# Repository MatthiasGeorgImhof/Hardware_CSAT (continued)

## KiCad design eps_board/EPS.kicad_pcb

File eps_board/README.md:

# Electric Power Supply (EPS) board

- STM32L496VGTx controller
- 2x CAN buses
- 2x 18650 LiPo batteries for operation and 1x CR2450 cell for RTC

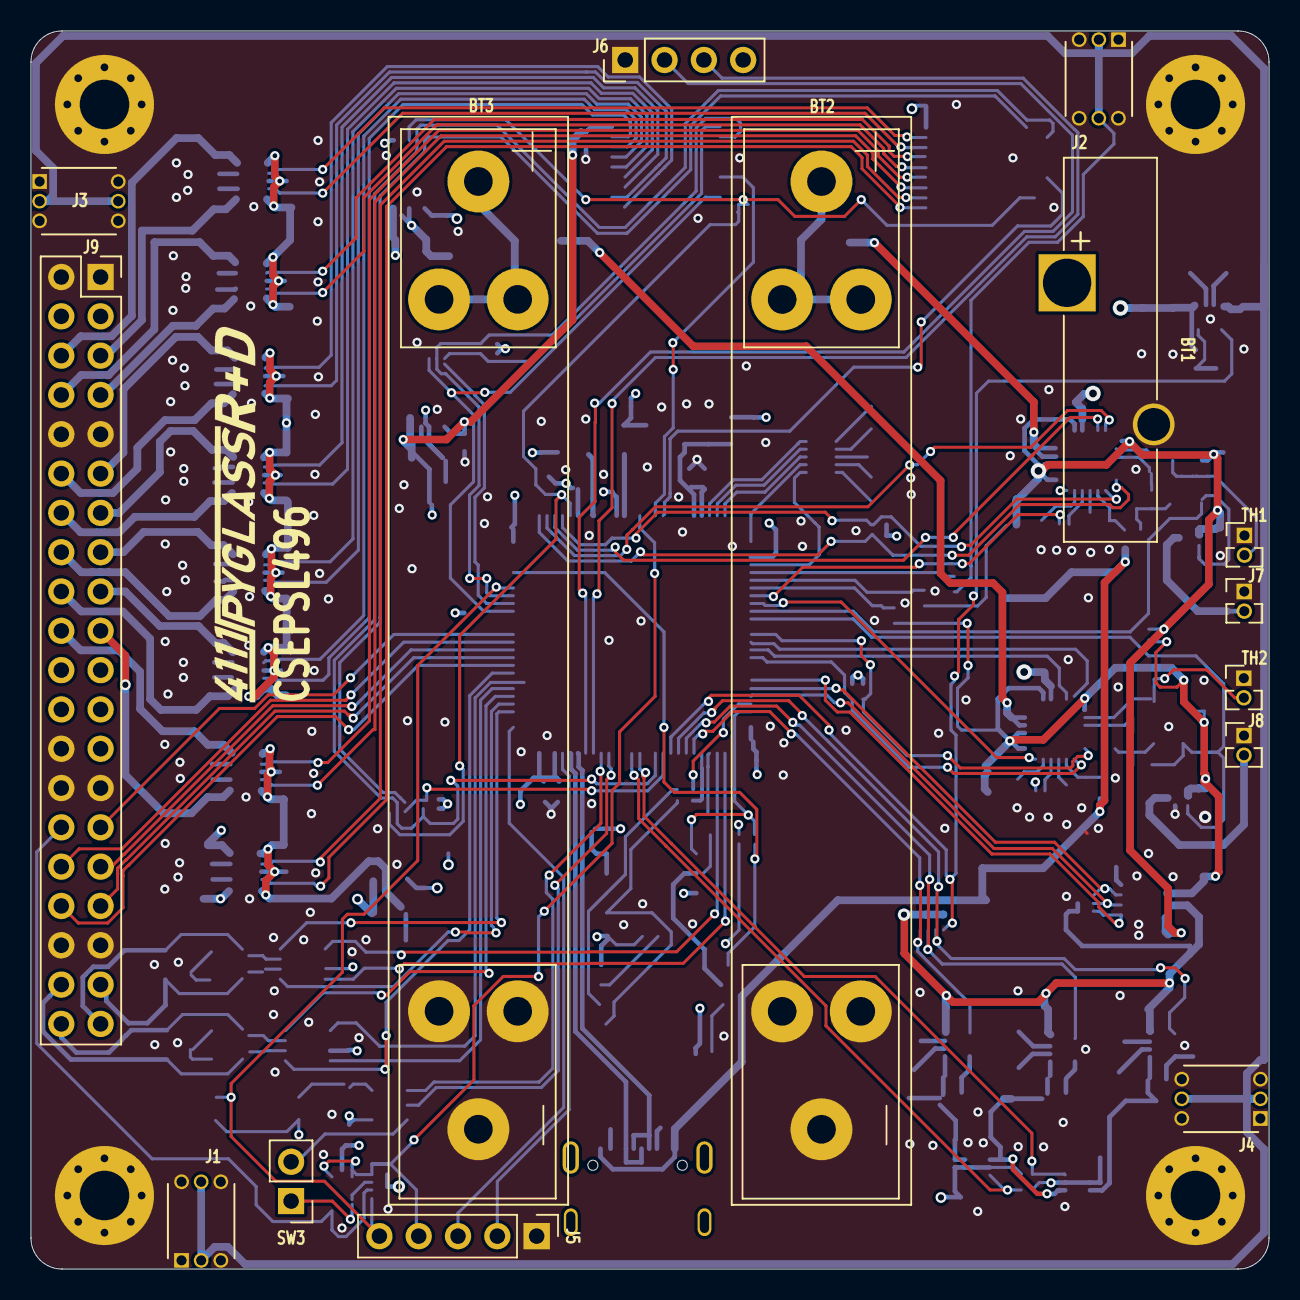
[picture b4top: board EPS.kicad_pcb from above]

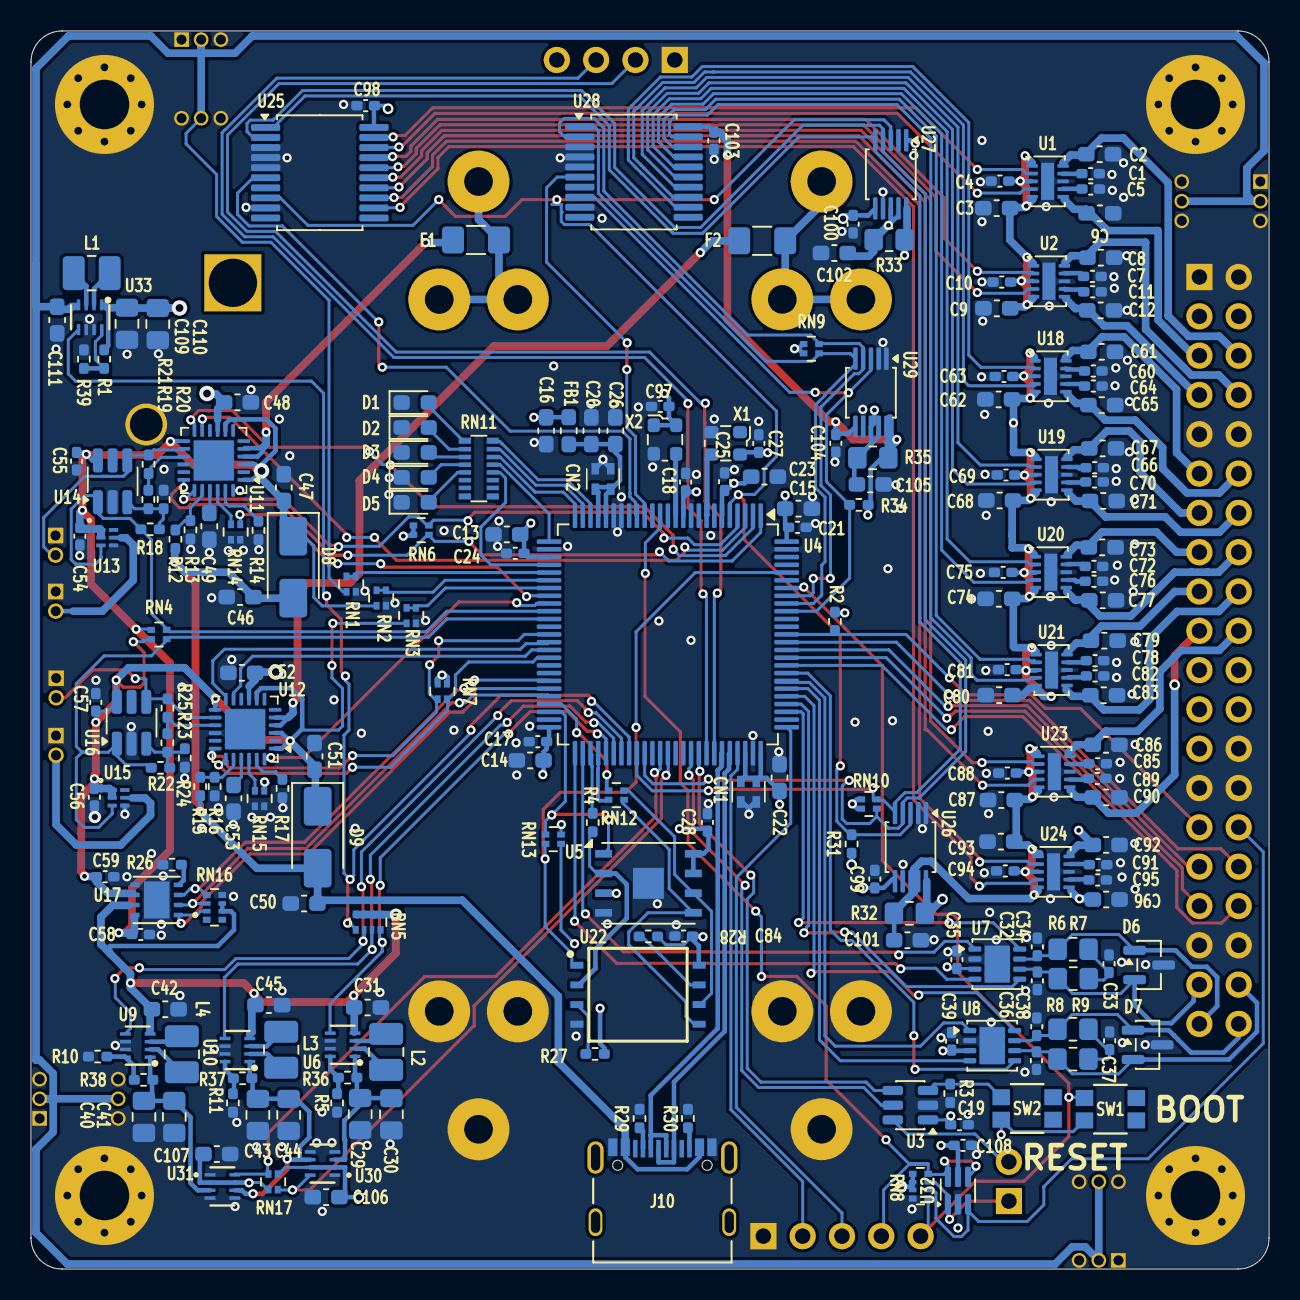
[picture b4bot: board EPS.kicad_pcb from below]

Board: 4 copper layers, 80.0 x 80.0 mm, 242 parts (223 on the bottom side), 187 nets.

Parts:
BT1: CR2450; Battery_Panasonic_CR2450-VAN_Vertical_CircularHoles
BT2, BT3: Battery_Cell; BatteryHolder_Keystone_54_v2_1x18650
C1, C5, C7, C11, C60, C64, C66, C70, C72, C76, C78, C82, C85, C89, C91, C95: 220pF; C_0402_1005Metric_Pad0.74x0.62mm_HandSolder
C2, C6, C8, C12, C61, C65, C67, C71, C73, C77, C79, C83, C86, C90, C92, C96: 10u; C_0603_1608Metric_Pad1.08x0.95mm_HandSolder
C3, C9, C62, C68, C74, C80, C87, C93: 22u; C_0603_1608Metric_Pad1.08x0.95mm_HandSolder
C4, C10, C27, C28, C35, C39, C63, C69, C75, C81, C84, C88, C94, C97, C108: 100n; C_0402_1005Metric_Pad0.74x0.62mm_HandSolder
C13, C14, C15, C16, C20, C22, C23, C26, C101, C102, C105, C106, C107: 10uF; C_0603_1608Metric_Pad1.08x0.95mm_HandSolder
C17, C18, C19, C21, C24, C25, C54, C55, C56, C57, C58, C59, C98, C99, C100, C103, C104: 100nF; C_0402_1005Metric_Pad0.74x0.62mm_HandSolder
C29, C30, C40, C41, C43, C44, C109, C110: 47uF; C_0805_2012Metric_Pad1.18x1.45mm_HandSolder
C31, C42, C45, C111: 22uF; C_0603_1608Metric_Pad1.08x0.95mm_HandSolder
C32, C34, C36, C38: 100p; C_0402_1005Metric_Pad0.74x0.62mm_HandSolder
C33, C37: 4n7; C_0402_1005Metric_Pad0.74x0.62mm_HandSolder
C46, C47, C48, C49, C50, C51, C52, C53: 4.7uF; C_0603_1608Metric_Pad1.08x0.95mm_HandSolder
CN1, CN2: 100nF; W2A2-X
D1: RED; LED_0603_1608Metric_Pad1.05x0.95mm_HandSolder
D2: GREEN; LED_0603_1608Metric_Pad1.05x0.95mm_HandSolder
D3, D4, D5: YELLOW; LED_0603_1608Metric_Pad1.05x0.95mm_HandSolder
D6, D7: NUP2105LT1G; SOT-23
D8, D9: NRVBA210LNT3G; D_SMA
F1, F2: Polyfuse; Fuse_1206_3216Metric_Pad1.42x1.75mm_HandSolder
FB1: 120R; L_0603_1608Metric_Pad1.05x0.95mm_HandSolder
H1, H2, H3, H4: MountingHole_Pad; MountingHole_3.2mm_M3_Pad_Via
J1, J2, J3, J4: Conn_02x03_Odd_Even; HARWIN_M50-3200345
J5: Conn_01x05_Pin Vertical; PinHeader_1x05_P2.54mm_Vertical
J6: Conn_01x04_Pin Vertical; PinHeader_1x04_P2.54mm_Vertical
J7, J8: Conn_01x02; PinHeader_1x02_P1.27mm_Vertical
J9: PC104 Conn_02x20_Odd_Even; PinSocket_2x20_P2.54mm_Vertical
J10: 10155435-00011LF; AMPHENOL_10155435-00011LF
L1, L2, L3, L4: 1uH; L_1008_2520Metric_Pad1.43x2.20mm_HandSolder
R1: 806K; R_0402_1005Metric_Pad0.72x0.64mm_HandSolder
R2: 330K; R_0402_1005Metric_Pad0.72x0.64mm_HandSolder
R3: 22K; R_0402_1005Metric_Pad0.72x0.64mm_HandSolder
R4: 22R; R_0402_1005Metric_Pad0.72x0.64mm_HandSolder
R5, R10, R11, R39: 91K; R_0402_1005Metric_Pad0.72x0.64mm_HandSolder
R6, R7, R8, R9: 60R4; R_0805_2012Metric_Pad1.20x1.40mm_HandSolder
R12, R15: 26.7K; R_0402_1005Metric_Pad0.72x0.64mm_HandSolder
R13, R16, R21, R25: 10K; R_0402_1005Metric_Pad0.72x0.64mm_HandSolder
R14, R17: 1M; R_0402_1005Metric_Pad0.72x0.64mm_HandSolder
R18, R22: DNP; R_0402_1005Metric_Pad0.72x0.64mm_HandSolder
R19, R23, R27, R28, R31, R34: 100K; R_0402_1005Metric_Pad0.72x0.64mm_HandSolder
R20, R24: 280K; R_0402_1005Metric_Pad0.72x0.64mm_HandSolder
R26: 330R; R_0402_1005Metric_Pad0.72x0.64mm_HandSolder
R29, R30: 5K1; R_0402_1005Metric_Pad0.72x0.64mm_HandSolder
R32, R33, R35: 10m; R_0805_2012Metric_Pad1.20x1.40mm_HandSolder
R36, R38: 511K; R_0402_1005Metric_Pad0.72x0.64mm_HandSolder
R37: 490K; R_0402_1005Metric_Pad0.72x0.64mm_HandSolder
RN1, RN2, RN3, RN4, RN6, RN7, RN13: 100K; R_Array_Convex_2x0402_widepads
RN5, RN8, RN16: 100K; R_Array_Convex_4x0402_widepads
RN9, RN10: 5K6; R_Array_Convex_2x0402_widepads
RN11: 1K; R_Array_Convex_8x0602_widepads
RN12: 22R; R_Array_Convex_2x0402_widepads
RN14, RN15, RN17: 10K; R_Array_Convex_2x0402_widepads
SW1, SW2: EVP-AA602W; EVP602AA
SW3: Conn_01x02_Pin Vertical; PinHeader_1x02_P2.54mm_Vertical
TH1, TH2: Thermistor_NTC; PinHeader_1x02_P1.27mm_Vertical
U1, U2, U18, U19, U20, U21, U23, U24: TPS22968QDMGRQ1; WSON-10-1EP_2x3mm_P0.5mm_EP0.84x2.4mm
U3: TPL5010; SOT-23-6
U4: STM32L496VGTx; LQFP-100_14x14mm_P0.5mm
U5: MR25H10; DFN-8-1EP_6x5mm_P1.27mm_EP2x2mm
U6, U9, U10, U33: TPS631000DRLR; TPS631000DRLR_TEX
U7, U8: TCAN3414; VSON-8-1EP_3x3mm_P0.65mm_EP1.65x2.4mm
U11, U12: LTC4066; QFN-24-1EP_4x4mm_P0.5mm_EP2.6x2.6mm
U13, U15: TPS22995; WQFN-HR6_RZG_TEX
U14, U16: MCP65R46; SOT-23-6_Handsoldering
U17: TPS2115ADRBR; SON65P300X300X100-9N
U22: MT29F4G01ABAFDWB-IT:F TR; SON127P800X600X65-8N
U25, U28: MCP23008T-E/SS; SSOP-20_5.3x7.2mm_P0.65mm
U26, U27: INA226AIDGSR; VSSOP-10_3x3mm_P0.5mm
U29: INA226; VSSOP-10_3x3mm_P0.5mm
U30, U31: LM66200DRLR; SOT-5X3_DRL_TEX
U32: 74LVC2G07; SOT-363_SC-70-6
X1: 32.768KHZ; Oscillator_SMD_ECS_2520MV-xxx-xx-4Pin_2.5x2.0mm
X2: 10MHz; Oscillator_SMD_ECS_2520MV-xxx-xx-4Pin_2.5x2.0mm

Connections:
+3V3: C103.1, C104.1, C107.1, R34.1, R35.1, RN17.3 (R2.2), U28.20 (VDD), U29.6 (VS), U29.10 (IN+), U31.2 (VOUT), U31.7 (VOUT)
+3V3_CORE: C13.1, C14.1, C15.1, C16.1, C17.1, C18.1, C19.1, C21.2, C22.2, C24.1, C27.1, C35.1, C39.1, C97.1, C98.1, C99.1, C100.1, C106.1, C108.2, CN1.1, CN1.2, FB1.1, J6.4, R2.1, R31.1, R32.1, RN6.1 (R1.1), RN6.2 (R2.1), RN7.1 (R1.1), RN7.2 (R2.1), RN8.5 (R4.2), RN8.6 (R3.2), RN8.7 (R2.2), RN9.1 (R1.1), RN9.2 (R2.1), RN10.1 (R1.1), RN10.2 (R2.1), RN17.1 (R1.1), SW1.2, SW2.2, U3.1 (VDD), U4.11 (VDD), U4.28 (VDD), U4.50 (VDD), U4.73 (VDDUSB), U4.75 (VDD), U4.100 (VDD), U7.3 (VCC), U8.3 (VCC), U25.20 (VDD), U26.6 (VS), U26.10 (IN+), U27.1 (A1), U27.6 (VS), U30.2 (VOUT), U30.7 (VOUT), U32.5 (VCC), X1.4 (VCC), X2.1 (TRI-STATE), X2.4 (VDD)
/3V3_1: C61.1, J9.11, U18.10 (VOUT1)
/3V3_2: C65.2, J9.12, U18.6 (VOUT2)
/3V3_3: C67.1, J9.13, U19.10 (VOUT1)
/3V3_4: C71.2, J9.14, U19.6 (VOUT2)
/3V3_5: C73.1, J9.15, U20.10 (VOUT1)
/3V3_6: C77.2, J9.16, U20.6 (VOUT2)
/3V3_7: C79.1, J9.17, U21.10 (VOUT1)
/3V3_8: C83.2, J9.18, U21.6 (VOUT2)
/3V3_9: C90.2, J9.19, U23.6 (VOUT2)
/3V3_10: C86.1, J9.20, U23.10 (VOUT1)
/3V3_EPS_FLASH: C84.1, C96.2, R27.1, R28.1, RN13.1 (R1.1), U22.8 (VCC), U24.6 (VOUT2)
/3V3_EPS_MRAM: C28.1, C92.1, RN13.2 (R2.1), U5.3 (~WP), U5.7 (~HOLD), U5.8 (VDD), U24.10 (VOUT1)
/*BC_1_CHRG: RN6.3 (R2.2), U4.1 (PE2), U11.18 (~CHRG)
/*BC_2_CHRG: RN7.3 (R2.2), U4.38 (PE7), U12.18 (~CHRG)
/*IDEAL_STATUS: RN16.3 (R3.1), U4.44 (PE13), U17.1 (STAT)
/ADC_SOLAR_RAW: RN1.3 (R2.2), RN1.4 (R1.2), U4.30 (PA5)
/ADC_VOUT1: RN2.3 (R2.2), RN2.4 (R1.2), U4.31 (PA6)
/ADC_VOUT2: RN3.3 (R2.2), RN3.4 (R1.2), U4.32 (PA7)
/ATTENTION: J9.29, R2.2, U4.88 (PD7)
/AVI_EXTRN_RST: J9.32, U4.87 (PD6)
/BATTERY_1/NTC: R21.2, TH1.2, U11.14 (NTC), U14.4 (-)
/BATTERY_1/VBAT: F1.1, U11.4 (BAT), U11.5 (BAT)
/BATTERY_1/VNTC: R19.1, R21.1, U11.15 (VNTC)
/BATTERY_2/NTC: R25.2, TH2.2, U12.14 (NTC), U16.4 (-)
/BATTERY_2/VBAT: F2.1, U12.4 (BAT), U12.5 (BAT)
/BATTERY_2/VNTC: R23.1, R25.1, U12.15 (VNTC)
/BATTERY_CHARGER_1/CLPROG: RN14.2 (R2.1), U11.22 (CLPROG)
/BATTERY_CHARGER_2/CLPROG: RN15.2 (R2.1), U12.22 (CLPROG)
/BATT_1: C6.2, J9.5, U1.6 (VOUT2)
/BATT_2: C2.1, J9.6, U1.10 (VOUT1)
/BATT_3: C12.2, J9.7, U2.6 (VOUT2)
/BATT_4: C8.1, J9.8, U2.10 (VOUT1)
/BC_1_ISTAT: RN14.1 (R1.1), U4.33 (PC4), U11.24 (ISTAT)
/BC_1_POL: RN6.4 (R1.2), U4.4 (PE5), U11.19 (POL)
/BC_1_SHDN: U4.2 (PE3), U11.12 (SHDN)
/BC_1_SUSP: U4.3 (PE4), U11.11 (SUSP)
/BC_2_ISTAT: RN15.1 (R1.1), U4.34 (PC5), U12.24 (ISTAT)
/BC_2_POL: RN7.4 (R1.2), U4.41 (PE10), U12.19 (POL)
/BC_2_SHDN: U4.39 (PE8), U12.12 (SHDN)
/BC_2_SUSP: U4.40 (PE9), U12.11 (SUSP)
/BOOT: J5.5, RN8.1 (R1.1), SW1.1, U4.94 (PH3)
/Boost Buck Regulator 5V1/LX1: L1.2, U33.3 (LX1)
/Boost Buck Regulator 5V1/LX2: L1.1, U33.2 (LX2)
/Boost Buck Regulator 5V1/R-: R1.2, R39.1, U33.8 (FB)
/CAN1_H: C36.1, D7.1 (K), J9.40, R8.1, U8.7 (CANH)
/CAN1_L: C38.2, D7.2 (K), J9.38, R9.2, U8.6 (CANL)
/CAN2_H: C32.1, D6.1 (K), J9.39, R6.1, U7.7 (CANH)
/CAN2_L: C34.2, D6.2 (K), J9.37, R7.2, U7.6 (CANL)
/COMM1_RST: J9.33, U4.85 (PD4)
/COMM2_RST: J9.34, U4.84 (PD3)
/EPS_EXTRN_RST: J9.30, RN8.2 (R2.1), U32.3 (IN2)
/HEATER1_ENABLED: R18.1, RN4.4 (R1.2), U4.35 (PB0), U13.3 (EN), U14.1
/HEATER2_ENABLED: R22.1, RN4.3 (R2.2), U4.36 (PB1), U15.3 (EN), U16.1
/I2C1_SCL: RN9.3 (R2.2), U4.92 (PB6), U28.1 (SCL), U29.5 (SCL)
/I2C1_SDA: RN9.4 (R1.2), U4.93 (PB7), U28.2 (SDA), U29.4 (SDA)
/I2C4_SCL: RN10.4 (R1.2), U4.59 (PD12), U25.1 (SCL), U26.5 (SCL), U27.5 (SCL)
/I2C4_SDA: RN10.3 (R2.2), U4.60 (PD13), U25.2 (SDA), U26.4 (SDA), U27.4 (SDA)
/I2C Power Switches 3VAUX/ENABLE_0: U18.2 (ON1), U28.12 (GP0)
/I2C Power Switches 3VAUX/ENABLE_1: U18.4 (ON2), U28.13 (GP1)
/I2C Power Switches 3VAUX/ENABLE_2: U19.2 (ON1), U28.14 (GP2)
/I2C Power Switches 3VAUX/ENABLE_3: U19.4 (ON2), U28.15 (GP3)
/I2C Power Switches 3VAUX/ENABLE_4: U20.2 (ON1), U28.16 (GP4)
/I2C Power Switches 3VAUX/ENABLE_5: U20.4 (ON2), U28.17 (GP5)
/I2C Power Switches 3VAUX/ENABLE_6: U21.2 (ON1), U28.18 (GP6)
/I2C Power Switches 3VAUX/ENABLE_7: U21.4 (ON2), U28.19 (GP7)
/I2C Power Switches 3VAUX/VBUS: C62.1, C63.1, C68.1, C69.1, C74.1, C75.1, C80.1, C81.1, C105.1, R35.2, U18.1 (VIN1), U18.3 (VBIAS), U18.5 (VIN2), U19.1 (VIN1), U19.3 (VBIAS), U19.5 (VIN2), U20.1 (VIN1), U20.3 (VBIAS), U20.5 (VIN2), U21.1 (VIN1), U21.3 (VBIAS), U21.5 (VIN2), U29.8 (VBUS), U29.9 (IN-)
/I2C Power Switches 3VCORE/3V3_METERED: C87.1, C88.1, C93.1, C94.1, C101.1, R32.2, U23.1 (VIN1), U23.3 (VBIAS), U23.5 (VIN2), U24.1 (VIN1), U24.3 (VBIAS), U24.5 (VIN2), U26.8 (VBUS), U26.9 (IN-)
/I2C Power Switches 3VCORE/ENABLE0: U24.4 (ON2), U25.12 (GP0)
/I2C Power Switches 3VCORE/ENABLE1: U24.2 (ON1), U25.13 (GP1)
/I2C Power Switches 3VCORE/ENABLE2: U23.4 (ON2), U25.14 (GP2)
/I2C Power Switches 3VCORE/ENABLE3: U23.2 (ON1), U25.15 (GP3)
/I2C Power Switches 3VCORE/ENABLE4: U2.4 (ON2), U25.16 (GP4)
/I2C Power Switches 3VCORE/ENABLE5: U2.2 (ON1), U25.17 (GP5)
/I2C Power Switches 3VCORE/ENABLE6: U1.4 (ON2), U25.18 (GP6)
/I2C Power Switches 3VCORE/ENABLE7: U1.2 (ON1), U25.19 (GP7)
/I2C Power Switches 3VCORE/VBUS_METERED: C3.1, C4.1, C9.1, C10.1, C102.1, R33.2, U1.1 (VIN1), U1.3 (VBIAS), U1.5 (VIN2), U2.1 (VIN1), U2.3 (VBIAS), U2.5 (VIN2), U27.8 (VBUS), U27.9 (IN-)
/IDEAL_DO0: RN16.2 (R2.1), U4.46 (PE15), U17.2 (D0)
/IDEAL_DO1: RN16.1 (R1.1), U4.45 (PE14), U17.3 (D1)
/INT_PS_3V3: R34.2, U4.91 (PB5), U28.8 (INT), U29.3 (ALERT)
/INT_PS_CORE_VBUS: R31.2, U4.5 (PE6), U25.8 (INT), U26.3 (ALERT), U27.3 (ALERT)
/NRST: J5.4, RN8.4 (R4.1), U4.14 (NRST), U32.4 (OUT2), U32.6 (OUT1)
/PMIC/CAN1_RX: U4.81 (PD0), U8.4 (RXD)
/PMIC/CAN1_SHDN: U4.83 (PD2), U8.5 (SHTD)
/PMIC/CAN1_STBY: U4.80 (PC12), U8.8 (STB)
/PMIC/CAN1_TX: U4.82 (PD1), U8.1 (TXD)
/PMIC/CAN2_RX: U4.51 (PB12), U7.4 (RXD)
/PMIC/CAN2_SHDN: U4.79 (PC11), U7.5 (SHTD)
/PMIC/CAN2_STBY: U4.78 (PC10), U7.8 (STB)
/PMIC/CAN2_TX: U4.52 (PB13), U7.1 (TXD)
/PMIC/HSE_CLK: U4.12 (PH0), X2.3 (OUTPUT)
/PMIC/LED_1: RN11.16 (R), U4.23 (PA0)
/PMIC/LED_2: RN11.15 (R), U4.24 (PA1)
/PMIC/LED_3: RN11.14 (R), U4.25 (PA2)
/PMIC/LED_4: RN11.13 (R), U4.26 (PA3)
/PMIC/LED_5: RN11.12 (R), U4.29 (PA4)
/PMIC/RCC_OSC32_IN: U4.8 (PC14), X1.3 (OUT)
/PMIC/SPI2_FLASH_CS: RN13.4 (R1.2), U4.96 (PB9), U22.1 (CS#)
/PMIC/SPI2_MISO: R4.2, U4.53 (PB14)
/PMIC/SPI2_MOSI: RN12.2 (R2.1), U4.54 (PB15)
/PMIC/SPI2_MRAM_CS: RN13.3 (R2.2), U4.48 (PB11), U5.1 (~CS)
/PMIC/SPI2_SCK: RN12.1 (R1.1), U4.47 (PB10)
/PMIC/SPI_MISO: R4.1, U5.2 (SO), U22.2 (SO/IO1)
/PMIC/SPI_MOSI: RN12.3 (R2.2), U5.5 (SI), U22.5 (SI/IO0)
/PMIC/SPI_SCK: RN12.4 (R1.2), U5.6 (SCK), U22.6 (SCK)
/PMIC/SWD_SWCLK: J5.3, U4.76 (PA14)
/PMIC/SWD_SWDIO: J5.2, U4.72 (PA13)
/PMIC/USART1_RX: J6.2, U4.69 (PA10)
/PMIC/USART1_TX: J6.3, U4.68 (PA9)
/PMIC/VDAA: C20.1, C26.2, CN2.1, CN2.2, FB1.2, U4.21 (VREF+), U4.22 (VDDA)
/POWER_3V3_RST: U4.16 (PC1), U28.6 (*RESET)
/POWER_CORE_VBUS_RST: U4.17 (PC2), U25.6 (*RESET)
/PWR3AUX_EN: RN5.3 (R3.1), U4.56 (PD9), U10.5 (EN)
/PWR3CORE_EN: RN5.4 (R4.1), U4.55 (PD8), U6.5 (EN)
/PWR3MAIN_EN: RN5.2 (R2.1), U4.57 (PD10), U9.5 (EN)
/Power Selector/Boost Buck Regulator 3V3/LX1: L2.2, U6.3 (LX1)
/Power Selector/Boost Buck Regulator 3V3/LX2: L2.1, U6.2 (LX2)
/Power Selector/Boost Buck Regulator 3V3/R+: C29.1, C30.1, R36.1, U6.1 (VOUT), U30.3 (VIN1)
/Power Selector/Boost Buck Regulator 3V3/R-: R5.1, R36.2, U6.8 (FB)
/Power Selector/Boost Buck Regulator 3V4/LX1: L4.2, U9.3 (LX1)
/Power Selector/Boost Buck Regulator 3V4/LX2: L4.1, U9.2 (LX2)
/Power Selector/Boost Buck Regulator 3V4/R+: C40.1, C41.1, R38.1, U9.1 (VOUT), U31.3 (VIN1)
/Power Selector/Boost Buck Regulator 3V4/R-: R10.1, R38.2, U9.8 (FB)
/Power Selector/Boost Buck Regulator 3V5/LX1: L3.2, U10.3 (LX1)
/Power Selector/Boost Buck Regulator 3V5/LX2: L3.1, U10.2 (LX2)
/Power Selector/Boost Buck Regulator 3V5/R+: C43.1, C44.1, R37.1, U10.1 (VOUT), U30.6 (VIN2), U31.6 (VIN2)
/Power Selector/Boost Buck Regulator 3V5/R-: R11.1, R37.2, U10.8 (FB)
/RST: RN8.3 (R3.1), SW3.1, U32.1 (IN1)
/SCI_EXTRN_RST: J9.31, U4.86 (PD5)
/SOLAR_EN: RN5.1 (R1.1), U4.58 (PD11), U33.5 (EN)
/STATUS_3V3: RN17.2 (R2.1), U4.62 (PD15), U31.8 (ST)
/STATUS_CORE: RN17.4 (R1.2), U4.63 (PC6), U30.8 (ST)
/USB_DN: J10.A7 (DN1_A), J10.B7 (DN2_B), U4.70 (PA11)
/USB_DP: J10.A6 (DP1_A), J10.B6 (DP2_B), U4.71 (PA12)
/VEXT: C46.1, C50.1, D8.2 (A), D9.2 (A), J10.A4_B9 (VBUS), J10.B4_A9 (VBUS__1), R12.2, R15.2
/VOUT1: C47.1, C54.1, C55.1, C58.2, D8.1 (K), RN2.1 (R1.1), RN4.1 (R1.1), U11.1 (OUT), U11.3 (OUT), U11.8 (OUT), U11.13 (HPWR), U13.1 (VBIAS), U13.2 (VIN), U14.6 (V+), U17.8 (IN1)
/VOUT2: C51.1, C56.1, C57.1, C59.2, D9.1 (K), RN3.1 (R1.1), RN4.2 (R2.1), U12.1 (OUT), U12.3 (OUT), U12.8 (OUT), U12.13 (HPWR), U15.1 (VBIAS), U15.2 (VIN), U16.6 (V+), U17.6 (IN2)
/VSOLAR_5V: C48.1, C52.1, C109.1, C110.1, R1.1, U11.9 (IN), U12.9 (IN), U33.1 (VOUT)
/VSOLAR_RAW: C111.1, J1.3, J1.4, J2.3, J2.4, J3.3, J3.4, J4.3, J4.4, RN1.1 (R1.1), U33.4 (VIN)
/WATCHDOG_DONE: U3.4 (DONE), U4.67 (PA8)
/WATCHDOG_WAKE: U3.5 (WAKE), U4.66 (PC9)
GND: BT1.2 (-), BT2.2 (-), BT3.2 (-), C1.2, C2.2, C3.2, C4.2, C5.1, C6.1, C7.2, C8.2, C9.2, C10.2, C11.1, C12.1, C13.2, C14.2, C15.2, C16.2, C17.2, C18.2, C19.2, C20.2, C21.1, C22.1, C23.2, C24.2, C25.2, C26.1, C27.2, C28.2, C29.2, C30.2, C31.2, C32.2, C33.2, C34.1, C35.2, C36.2, C37.2, C38.1, C39.2, C40.2, C41.2, C42.2, C43.2, C44.2, C45.2, C46.2, C47.2, C48.2, C49.2, C50.2, C51.2, C52.2, C53.2, C54.2, C55.2, C56.2, C57.2, C58.1, C59.1, C60.2, C61.2, C62.2, C63.2, C64.1, C65.1, C66.2, C67.2, C68.2, C69.2, C70.1, C71.1, C72.2, C73.2, C74.2, C75.2, C76.1, C77.1, C78.2, C79.2, C80.2, C81.2, C82.1, C83.1, C84.2, C85.2, C86.2, C87.2, C88.2, C89.1, C90.1, C91.2, C92.2, C93.2, C94.2, C95.1, C96.1, C97.2, C98.2, C99.2, C100.2, C101.2, C102.2, C103.2, C104.2, C105.2, C106.2, C107.2, C108.1, C109.2, C110.2, C111.2, CN1.3, CN1.4, CN2.3, CN2.4, D1.1 (K), D2.1 (K), D3.1 (K), D4.1 (K), D5.1 (K), D6.3 (A), D7.3 (A), H1.1, H2.1, H3.1, H4.1, J1.1, J1.2, J1.5, J1.6, J2.1, J2.2, J2.5, J2.6, J3.1, J3.2, J3.5, J3.6, J4.1, J4.2, J4.5, J4.6, J5.1, J6.1, J7.1, J8.1, J9.1, J9.2, J9.9, J9.10, J9.26, J9.27, J9.28, J9.35, J9.36, J10.A1_B12 (GND), J10.B1_A12 (GND__1), R3.2, R5.2, R10.2, R11.2, R13.1, R14.1, R16.1, R17.1, R20.2, R24.2, R26.2, R29.2, R30.1, R39.2, RN1.2 (R2.1), RN2.2 (R2.1), RN3.2 (R2.1), RN8.8 (R1.2), RN14.3 (R2.2), RN14.4 (R1.2), RN15.3 (R2.2), RN15.4 (R1.2), RN16.8 (R1.2), TH1.1, TH2.1, U1.8 (GND), U1.11 (TPAD), U2.8 (GND), U2.11 (TPAD), U3.2 (GND), U4.10 (VSS), U4.19 (VSSA), U4.20 (VREF-), U4.27 (VSS), U4.49 (VSS), U4.74 (VSS), U4.99 (VSS), U5.4 (VSS), U5.9 (PAD), U6.6 (MODE), U6.7 (GND), U7.2 (GND), U7.9 (GND), U8.2 (GND), U8.9 (GND), U9.6 (MODE), U9.7 (GND), U10.6 (MODE), U10.7 (GND), U11.16 (GND), U11.25 (GND), U12.16 (GND), U12.25 (GND), U13.4 (GND), U14.2 (V-), U15.4 (GND), U16.2 (V-), U17.5 (GND), U17.9 (EXP), U18.8 (GND), U18.11 (TPAD), U19.8 (GND), U19.11 (TPAD), U20.8 (GND), U20.11 (TPAD), U21.8 (GND), U21.11 (TPAD), U22.4 (VSS), U23.8 (GND), U23.11 (TPAD), U24.8 (GND), U24.11 (TPAD), U25.3 (A2), U25.4 (A1), U25.5 (A0), U25.9 (VSS), U26.1 (A1), U26.2 (A0), U26.7 (GND), U27.2 (A0), U27.7 (GND), U28.3 (A2), U28.4 (A1), U28.5 (A0), U28.9 (VSS), U29.1 (A1), U29.2 (A0), U29.7 (GND), U30.1 (GND), U30.4 (ON), U30.5 (GND), U31.1 (GND), U31.4 (ON), U31.5 (GND), U32.2 (GND), U33.6 (MODE), U33.7 (GND), X1.2 (GND), X2.2 (GND)
unnamed: BT1.1 (+), C23.1, C25.1, U4.6 (VBAT)
unnamed: BT2.1 (+), F1.2
unnamed: BT3.1 (+), F2.2
unnamed: C33.1, R6.2, R7.1
unnamed: C37.1, R8.2, R9.1
unnamed: D1.2 (A), RN11.1 (R)
unnamed: D2.2 (A), RN11.2 (R)
unnamed: D3.2 (A), RN11.3 (R)
unnamed: D4.2 (A), RN11.4 (R)
unnamed: D5.2 (A), RN11.5 (R)
unnamed: J7.2, U13.5 (VOUT)
unnamed: J8.2, U15.5 (VOUT)
unnamed: J10.A5 (CC1_A), R29.1
unnamed: J10.B5 (CC2_B), R30.2
unnamed: C1.1, U1.9 (CT1)
unnamed: C5.2, U1.7 (CT2)
unnamed: C7.1, U2.9 (CT1)
unnamed: C11.2, U2.7 (CT2)
unnamed: R3.1, SW2.1, U3.3 (DELAY/M_RST)
unnamed: SW3.2, U3.6 (~RST)
unnamed: R14.2, U11.23 (PROG)
unnamed: C49.1, U11.21 (TIMER)
unnamed: R12.1, R13.2, U11.20 (WALL)
unnamed: R17.2, U12.23 (PROG)
unnamed: C53.1, U12.21 (TIMER)
unnamed: R15.1, R16.2, U12.20 (WALL)
unnamed: R18.2, R19.2, R20.1, U14.3 (+)
unnamed: R22.2, R23.2, R24.1, U16.3 (+)
unnamed: R26.1, U17.4 (ILIM)
unnamed: C60.1, U18.9 (CT1)
unnamed: C64.2, U18.7 (CT2)
unnamed: C66.1, U19.9 (CT1)
unnamed: C70.2, U19.7 (CT2)
unnamed: C72.1, U20.9 (CT1)
unnamed: C76.2, U20.7 (CT2)
unnamed: C78.1, U21.9 (CT1)
unnamed: C82.2, U21.7 (CT2)
unnamed: R28.2, U22.7 (HOLD#/IO3)
unnamed: R27.2, U22.3 (WP#/IO2)
unnamed: C85.1, U23.9 (CT1)
unnamed: C89.2, U23.7 (CT2)
unnamed: C91.1, U24.9 (CT1)
unnamed: C95.2, U24.7 (CT2)
VBUS: C31.1, C42.1, C45.1, J9.3, J9.4, R33.1, RN5.5 (R4.2), RN5.6 (R3.2), RN5.7 (R2.2), RN5.8 (R1.2), RN16.6 (R3.2), RN16.7 (R2.2), U6.4 (VIN), U9.4 (VIN), U10.4 (VIN), U17.7 (OUT), U27.10 (IN+)

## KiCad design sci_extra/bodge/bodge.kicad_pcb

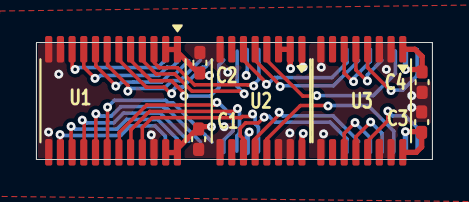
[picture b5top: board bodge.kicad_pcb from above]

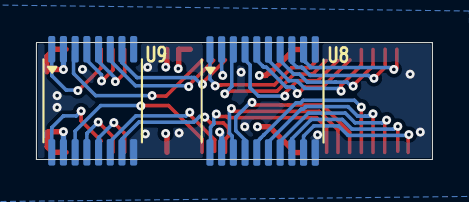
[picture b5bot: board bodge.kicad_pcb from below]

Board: 4 copper layers, 22.0 x 6.5 mm, 9 parts (2 on the bottom side), 31 nets.

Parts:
C1, C2, C3, C4: 1uF; C_0402_1005Metric_Pad0.74x0.62mm_HandSolder
U1: SN74AVC8T245PWR; TSSOP-24_4.4x7.8mm_P0.65mm
U2, U3: SN74AVC4T245PW; TSSOP-16_4.4x5mm_P0.65mm
U8: TXB0108PWR; TSSOP-20_4.4x6.5mm_P0.65mm_Flipped
U9: TXB0106PWR; TSSOP-16_4.4x5mm_P0.65mm_Flipped

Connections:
/1V8: C2.1, C4.1, U1.1 (V_{CCA}), U1.2 (DIR), U2.1 (VCCA), U3.1 (VCCA), U8.2 (VCCA), U9.2 (VCCA)
/3V3: C1.1, C3.1, U1.23 (V_{CCB}), U1.24 (V_{CCB}), U2.2 (1DIR), U2.3 (2DIR), U2.16 (VCCB), U3.16 (VCCB), U8.19 (VCCB), U9.15 (VCCB)
/GND: C1.2, C2.2, C3.2, C4.2, U1.11 (GND), U1.12 (GND), U1.13 (GND), U1.22 (~OE), U2.8 (GND), U2.9 (GND), U2.14 (2~OE), U2.15 (1~OE), U3.2 (1DIR), U3.3 (2DIR), U3.8 (GND), U3.9 (GND), U3.14 (2~OE), U3.15 (1~OE), U8.11 (GND), U9.9 (GND)
unnamed: U1.3 (A1), U8.1 (A1)
unnamed: U1.4 (A2), U8.3 (A2)
unnamed: U1.5 (A3), U8.4 (A3)
unnamed: U1.6 (A4), U8.5 (A4)
unnamed: U1.7 (A5), U8.6 (A5)
unnamed: U1.8 (A6), U8.7 (A6)
unnamed: U1.9 (A7), U8.8 (A7)
unnamed: U1.10 (A8), U8.9 (A8)
unnamed: U1.21 (B1), U8.20 (B1)
unnamed: U1.20 (B2), U8.18 (B2)
unnamed: U1.19 (B3), U8.17 (B3)
unnamed: U1.18 (B4), U8.16 (B4)
unnamed: U1.17 (B5), U8.15 (B5)
unnamed: U1.16 (B6), U8.14 (B6)
unnamed: U1.15 (B7), U8.13 (B7)
unnamed: U1.14 (B8), U8.12 (B8)
unnamed: U2.4 (1A1), U9.3 (A2)
unnamed: U2.5 (1A2), U9.6 (A5)
unnamed: U2.13 (1B1), U9.14 (B2)
unnamed: U2.12 (1B2), U9.11 (B5)
unnamed: U2.6 (2A1), U9.7 (A6)
unnamed: U2.11 (2B1), U9.10 (B6)
unnamed: U3.4 (1A1), U9.1 (A1)
unnamed: U3.5 (1A2), U9.4 (A3)
unnamed: U3.13 (1B1), U9.16 (B1)
unnamed: U3.12 (1B2), U9.13 (B3)
unnamed: U3.6 (2A1), U9.5 (A4)
unnamed: U3.11 (2B1), U9.12 (B4)
